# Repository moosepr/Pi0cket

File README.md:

# Pi0cket
slightly more advanced, pi zero based gameboy style interface board

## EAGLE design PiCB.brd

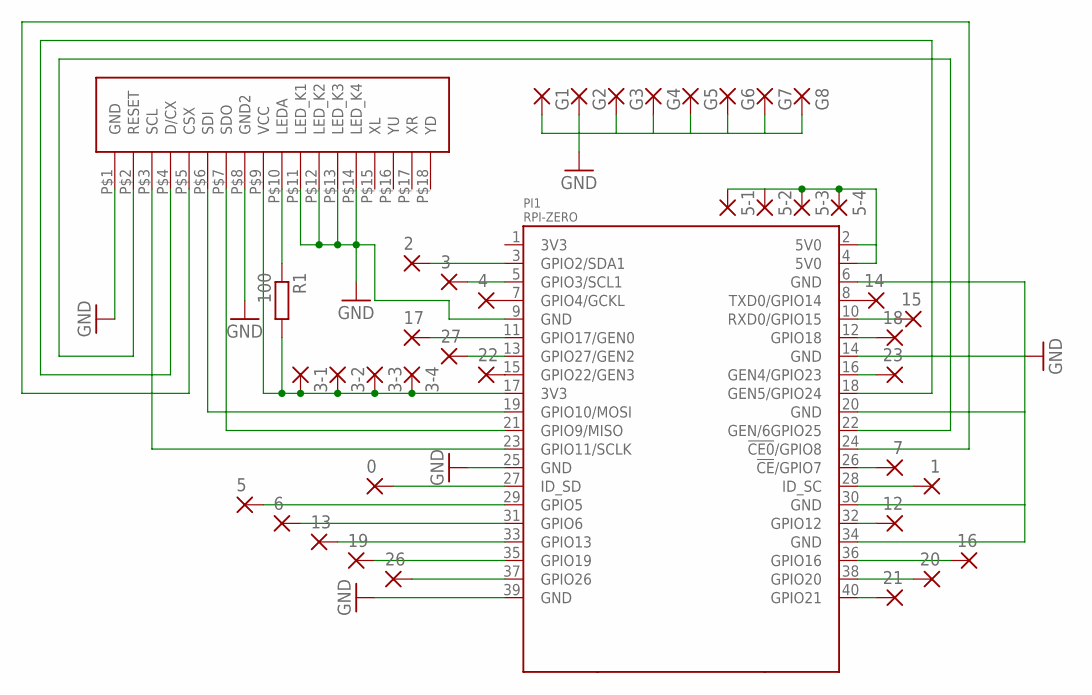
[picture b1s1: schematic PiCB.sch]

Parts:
0, 1, 2, 3, 3-1, 3-2, 3-3, 3-4, 4, 5, 5-1, 5-2, 5-3, 5-4, 6, 7, 12, 13, 14, 15, 16, 17, 18, 19, 20, 21, 22, 23, 26, 27: 1,6/0,8
G1, G2, G3, G4, G5, G6, G7, G8: 1,6/0,8
PI1: RPI-ZERO; RASPBERRYPI_BASTELSTUBE_V13_RASPI_BOARD_B+_FULL
R1: 100; R0805
U$2: ILI9341-2.8

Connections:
5V0@2: 5-1.1, 5-2.1, 5-3.1, 5-4.1, PI1.2 (5V0), PI1.4 (5V0)
GND: G1.1, G2.1, G3.1, G4.1, G5.1, G6.1, G7.1, G8.1, PI1.39 (GND), U$2.P$1 (GND), U$2.P$8 (GND2)
GND@1: PI1.9 (GND), U$2.P$11 (LED_K1), U$2.P$12 (LED_K2), U$2.P$13 (LED_K3), U$2.P$14 (LED_K4)
GND@2: PI1.25 (GND)
GND@7: PI1.6 (GND), PI1.14 (GND), PI1.20 (GND), PI1.30 (GND), PI1.34 (GND)
unnamed: PI1.22 (GEN/6GPIO25), U$2.P$2 (RESET)
unnamed: PI1.23 (GPIO11/SCLK), U$2.P$3 (SCL)
unnamed: PI1.19 (GPIO10/MOSI), U$2.P$6 (SDI)
unnamed: PI1.21 (GPIO9/MISO), U$2.P$7 (SDO)
unnamed: R1.1, U$2.P$10 (LEDA)
unnamed: PI1.18 (GEN5/GPIO24), U$2.P$4 (D/CX)
unnamed: PI1.24 (!CE0!/GPIO8), U$2.P$5 (CSX)
unnamed: 26.1, PI1.37 (GPIO26)
unnamed: 19.1, PI1.35 (GPIO19)
unnamed: 13.1, PI1.33 (GPIO13)
unnamed: 6.1, PI1.31 (GPIO6)
unnamed: 5.1, PI1.29 (GPIO5)
unnamed: 21.1, PI1.40 (GPIO21)
unnamed: 20.1, PI1.38 (GPIO20)
unnamed: 16.1, PI1.36 (GPIO16)
unnamed: 12.1, PI1.32 (GPIO12)
unnamed: 7.1, PI1.26 (!CE!/GPIO7)
unnamed: 14.1, PI1.8 (TXD0/GPIO14)
unnamed: 3-1.1, 3-2.1, 3-3.1, 3-4.1, PI1.17 (3V3), R1.2, U$2.P$9 (VCC)
unnamed: 23.1, PI1.16 (GEN4/GPIO23)
unnamed: 18.1, PI1.12 (GPIO18)
unnamed: 15.1, PI1.10 (RXD0/GPIO15)
unnamed: 22.1, PI1.15 (GPIO22/GEN3)
unnamed: 4.1, PI1.7 (GPIO4/GCKL)
unnamed: 27.1, PI1.13 (GPIO27/GEN2)
unnamed: 17.1, PI1.11 (GPIO17/GEN0)
unnamed: 3.1, PI1.5 (GPIO3/SCL1)
unnamed: 2.1, PI1.3 (GPIO2/SDA1)
unnamed: 0.1, PI1.27 (ID_SD)
unnamed: 1.1, PI1.28 (ID_SC)

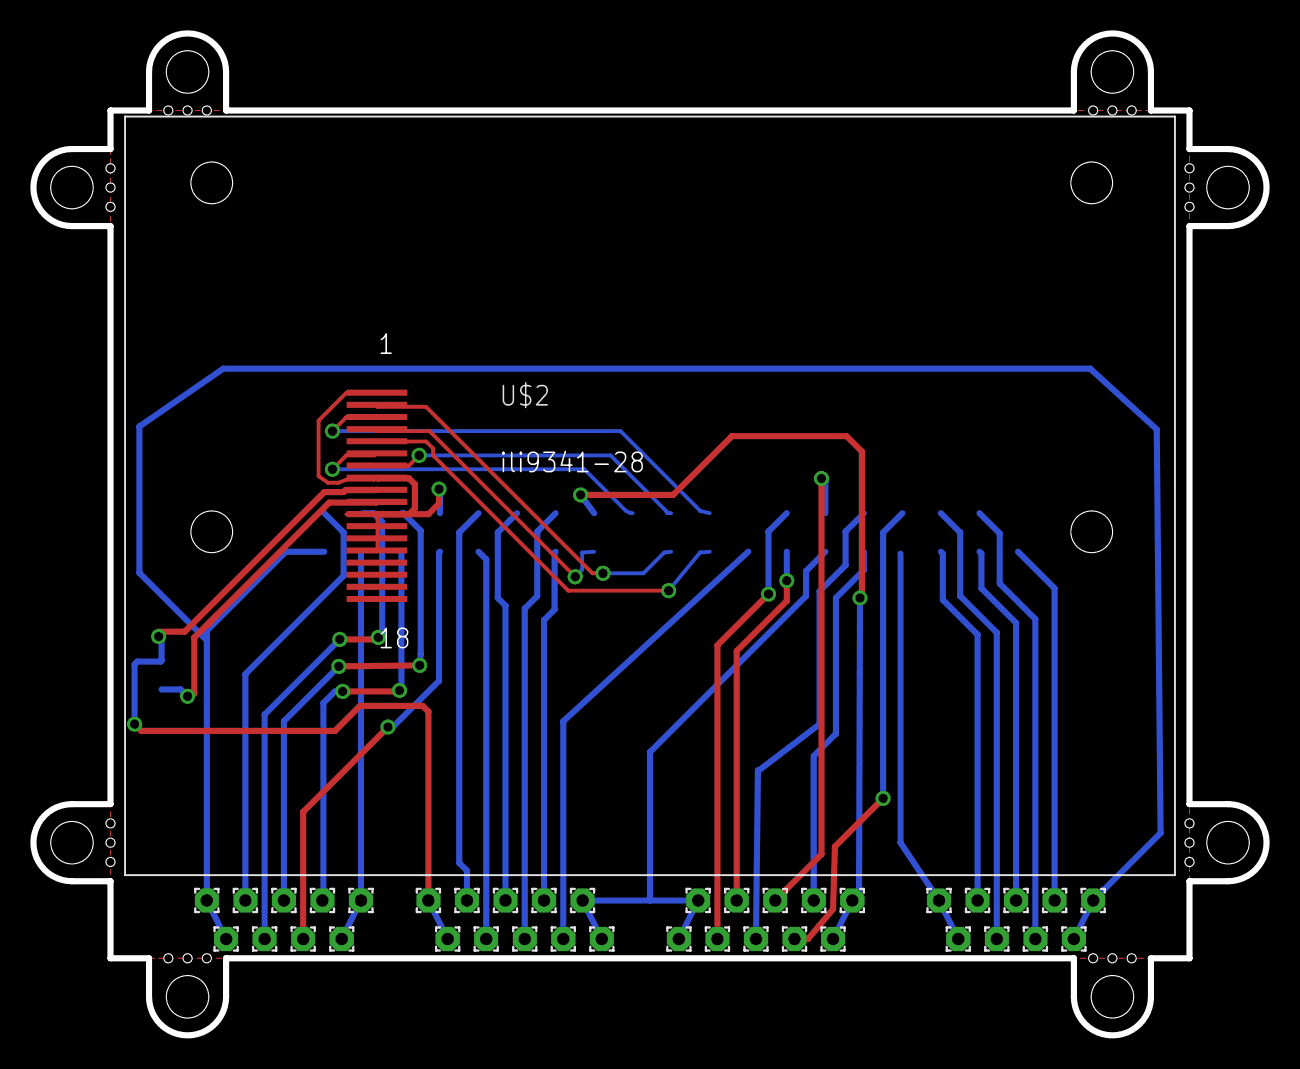
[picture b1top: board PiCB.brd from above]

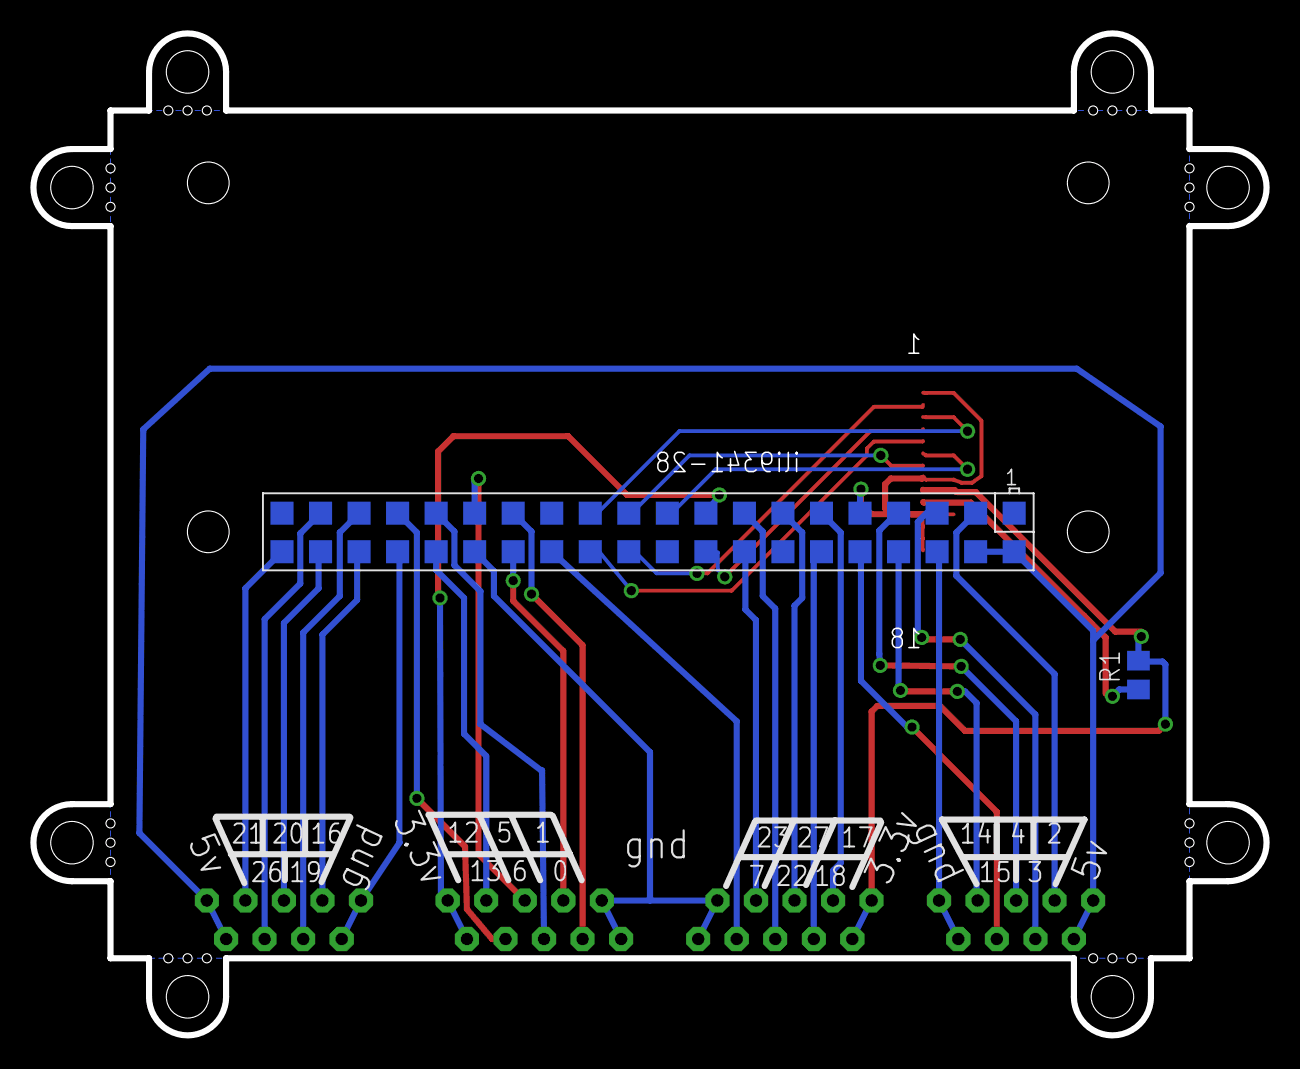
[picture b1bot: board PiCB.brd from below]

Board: 2 copper layers, 81.3 x 66.0 mm, 41 parts (2 on the bottom side), 34 nets.

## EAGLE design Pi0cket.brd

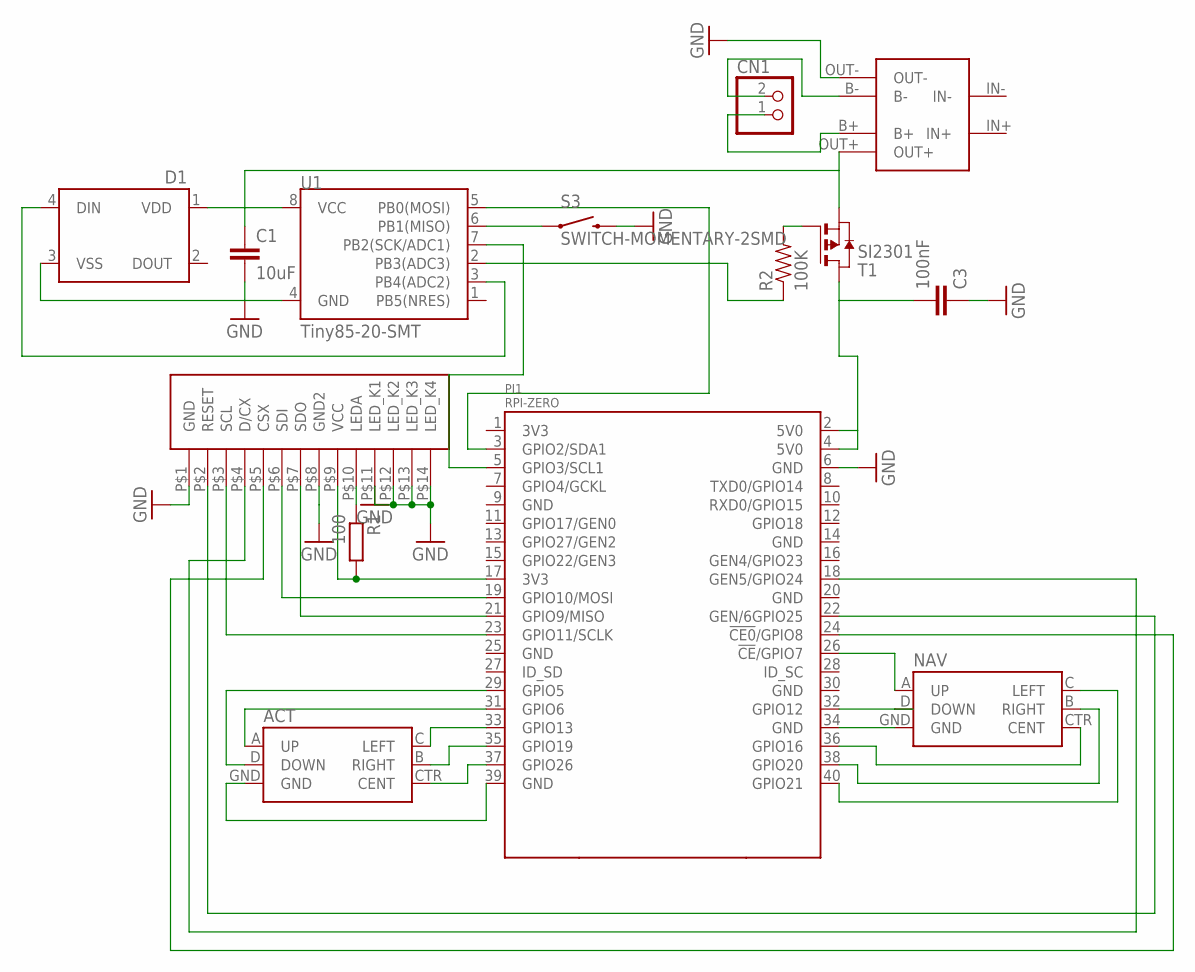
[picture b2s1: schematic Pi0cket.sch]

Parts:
ACT: JOYSTICK_MINI
C1: 10uF; C0603K
C3: 100nF; C0603K
CN1: JST_2PIN-SMT-RA; JST-PH-2-SMT-RA
D1: WS2812B
NAV: JOYSTICK_MINI
PI1: RPI-ZERO; RASPBERRYPI_BASTELSTUBE_V13_RASPI_BOARD_B+_FULL
POWER1: 03962A
R1: 100; R0805
R2: 100K; 0603-RES
S3: SWITCH-MOMENTARY-2SMD; TACTILE-SWITCH-SMD
SCREEN1: ILI9341-2.2
T1: SI2301; SOT-23
U1: Tiny85-20-SMT; SO08-EIAJ

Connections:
5V0@2: C3.2, PI1.2 (5V0), PI1.4 (5V0), T1.1 (D)
GND: C1.2, C3.1, D1.3 (VSS), PI1.6 (GND), POWER1.OUT-, S3.3 (2), SCREEN1.P$1 (GND), SCREEN1.P$8 (GND2), SCREEN1.P$11 (LED_K1), SCREEN1.P$12 (LED_K2), SCREEN1.P$13 (LED_K3), SCREEN1.P$14 (LED_K4), U1.4 (GND)
GND@3: ACT.GND, PI1.39 (GND)
GND@7: NAV.GND, PI1.34 (GND)
unnamed: PI1.22 (GEN/6GPIO25), SCREEN1.P$2 (RESET)
unnamed: PI1.23 (GPIO11/SCLK), SCREEN1.P$3 (SCL)
unnamed: PI1.19 (GPIO10/MOSI), SCREEN1.P$6 (SDI)
unnamed: PI1.21 (GPIO9/MISO), SCREEN1.P$7 (SDO)
unnamed: R1.1, SCREEN1.P$10 (LEDA)
unnamed: PI1.18 (GEN5/GPIO24), SCREEN1.P$4 (D/CX)
unnamed: PI1.24 (!CE0!/GPIO8), SCREEN1.P$5 (CSX)
unnamed: NAV.CTR (CENT), PI1.36 (GPIO16)
unnamed: ACT.CTR (CENT), PI1.37 (GPIO26)
unnamed: ACT.B (RIGHT), PI1.35 (GPIO19)
unnamed: ACT.C (LEFT), PI1.33 (GPIO13)
unnamed: ACT.A (UP), PI1.31 (GPIO6)
unnamed: ACT.D (DOWN), PI1.29 (GPIO5)
unnamed: NAV.B (RIGHT), PI1.38 (GPIO20)
unnamed: NAV.C (LEFT), PI1.40 (GPIO21)
unnamed: S3.1, U1.6 (PB1(MISO))
unnamed: NAV.D (DOWN), PI1.32 (GPIO12)
unnamed: NAV.A (UP), PI1.26 (!CE!/GPIO7)
unnamed: PI1.17 (3V3), R1.2, SCREEN1.P$9 (VCC)
unnamed: R2.1, U1.2 (PB3(ADC3))
unnamed: R2.2, T1.3 (G)
unnamed: CN1.1 (2), POWER1.B+
unnamed: PI1.3 (GPIO2/SDA1), U1.5 (PB0(MOSI))
unnamed: D1.4 (DIN), U1.3 (PB4(ADC2))
unnamed: C1.1, D1.1 (VDD), POWER1.OUT+, T1.2 (S), U1.8 (VCC)
unnamed: PI1.5 (GPIO3/SCL1), U1.7 (PB2(SCK/ADC1))
unnamed: CN1.2 (1), POWER1.B-

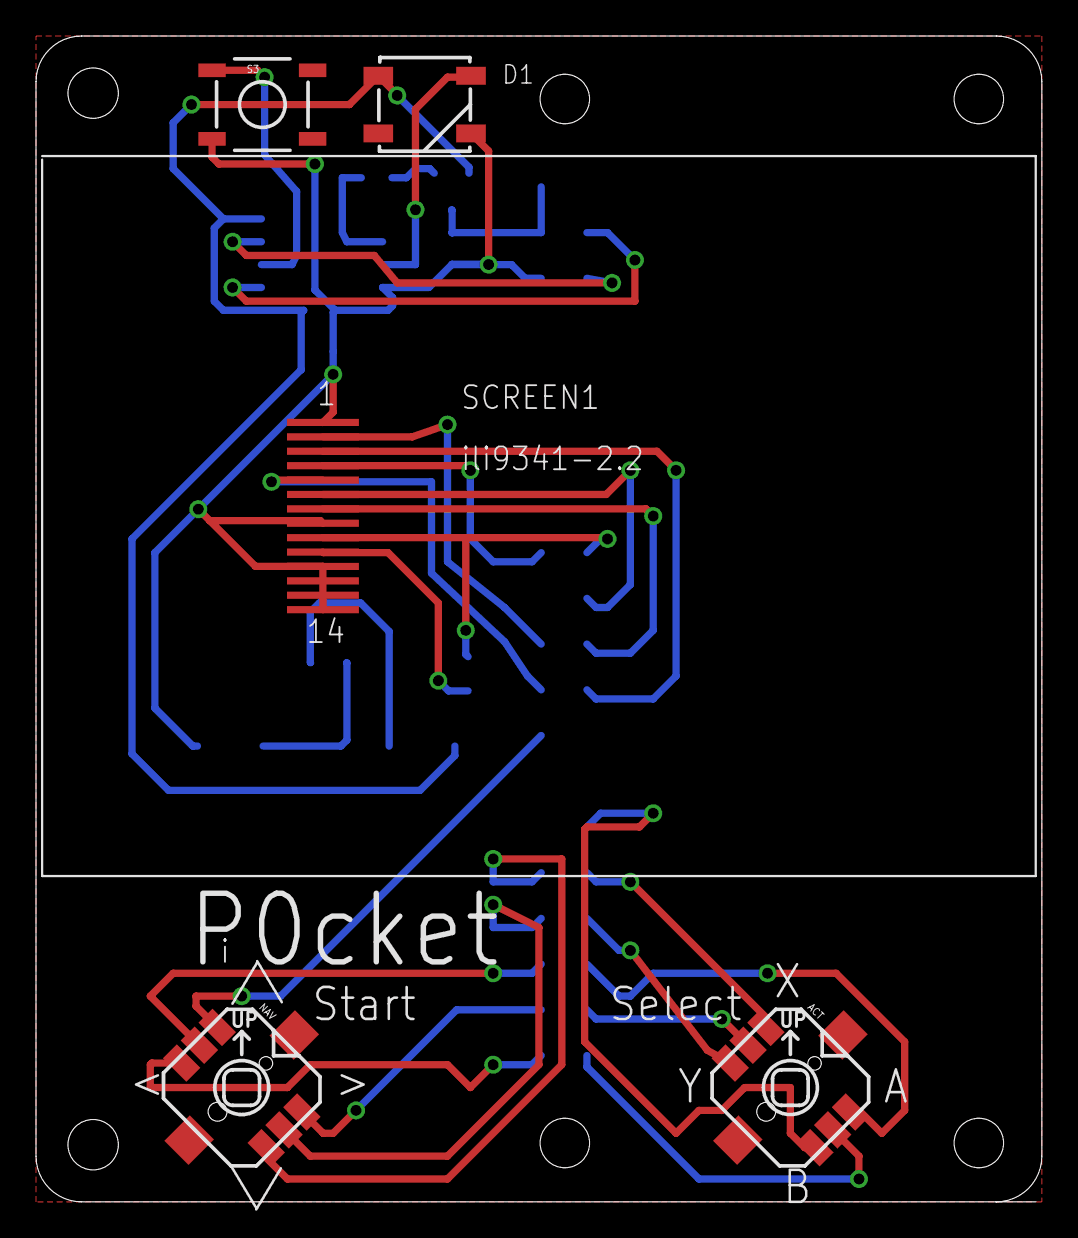
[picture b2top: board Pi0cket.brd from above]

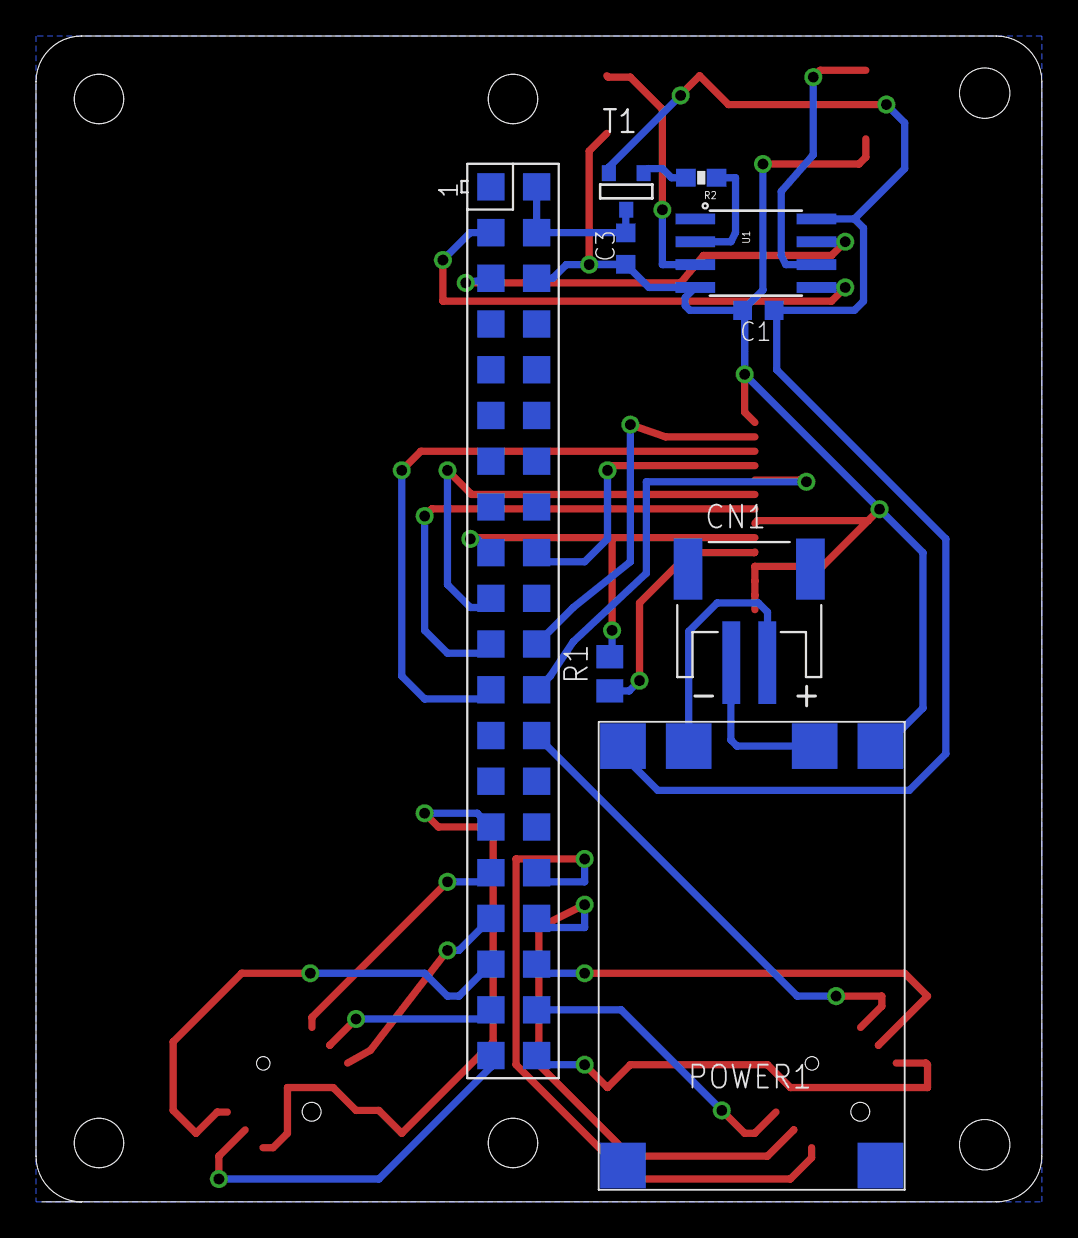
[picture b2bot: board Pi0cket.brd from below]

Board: 2 copper layers, 55.9 x 64.8 mm, 14 parts (9 on the bottom side), 31 nets.

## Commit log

2017-01-30 inital files
    added attiny power control with neopixel and FET
2017-01-30 arduino code
    early beginings of power control code
2017-02-03 some tweaks
    added i2c lines from the attiny to the pi (might live to regret that!!)
    re-arranged the tiny and associated bits to make things flow better
    added battery socket back in for ease of external charging
    moved backlight resistor to save some space
2017-02-25 Add files via upload
    straightened out some traces and moved the gpio silkscreen to the back
2017-02-25 Delete PiCB.brd
    wrong folder
2017-02-25 Delete PiCB.sch
    wrong folder!!!

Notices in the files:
parts and their libraries:
SparkFun-Electromechanical: Licensing: Creative Commons ShareAlike 4.0 International - https://creativecommons.org/licenses/by-sa/4.0
SparkFun-Passives: Licensing: CC v3.0 Share-Alike You are welcome to use this library for commercial purposes.
